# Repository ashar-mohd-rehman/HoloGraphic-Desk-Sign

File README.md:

# HoloGraphic-Desk-Sign
# Assembly 

a holographic desk sign which uses usb c as its power source and displays cool holograms. Custom edge-lit acrylic desk sign displaying death star. Powered via a 5V USB-C interface with low-current 470ohm resistors for safe and cool desk lamp. It sits inside a custom designed 3d printed case with slot to change the sign and a push button to switch it on/off

# PCB 

# Schematic

# case

# Laser Sign 

Bom Link : https://docs.google.com/spreadsheets/d/16aCT9J3KGzLhZE3Ovagxlka1-57kigsySBzX7_v0wDE/edit?usp=sharing

# Bill of Materials (BOM)

| Item | Quantity | Price (USD) | Link |
|------|----------|-------------|------|
| USB Type-C 16-Pin | 1 | $0.41 | [Buy](https://robu.in/product/type-c-31-m-12-hroparts-5a-1-16p-female-type-c-smd-usb-connectors-rohs/) |
| 12mm Tactile Push Button | 10 | $0.47 | [Buy](https://robu.in/product/12x12x12mm-tactile-push-button-switch-10pcs/) |
| LED Kit | 500 | $3.70 | [Buy](https://robu.in/product/pro-range-500pcs-5-colors-f5-mm-led-kit/) |
| 470Ω Resistor | 10 | $0.11 | [Buy](https://robu.in/product/470-ohm-0-25w-metal-film-resistor-pack-of-100/) |
| 5.1kΩ Resistor | 10 | $0.24 | [Buy](https://robu.in/product/mccfr0s2j0512a20-multicomp-pro-carbon-film-resistor-5-1kohm-500mw-5/) |
| PCB | 5 | $2.00 | [JLCPCB Quote](https://cart.jlcpcb.com/quote) |
| SLA Resin 3D Printed Sign | 1 | $2.91 | [JLC3DP Quote](https://jlc3dp.com/3d-printing-quote) |
| Printing Legion Case Estimate | 1 | $1.00 | Printing Estimate |

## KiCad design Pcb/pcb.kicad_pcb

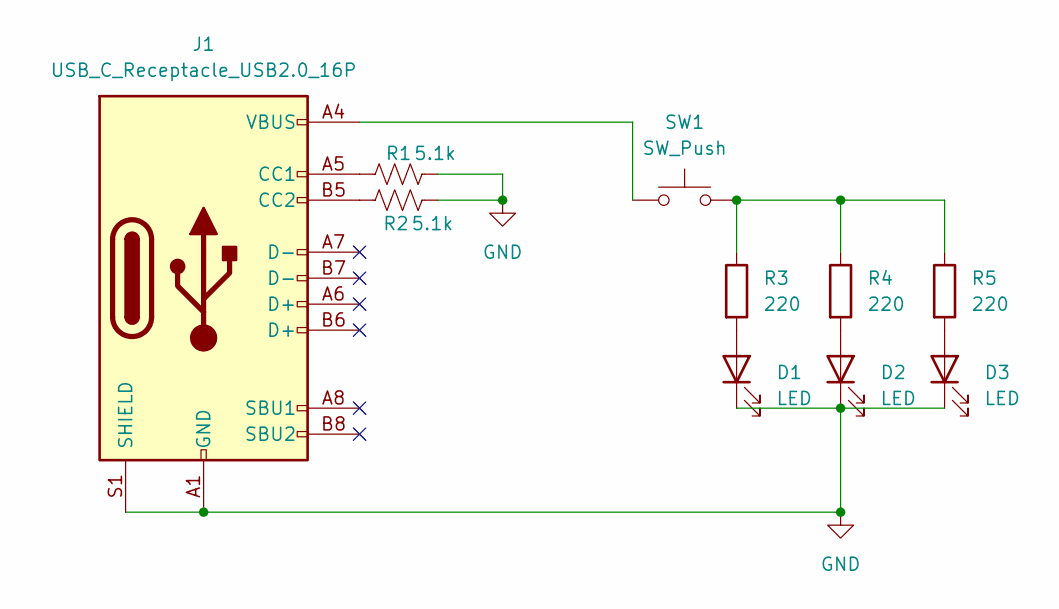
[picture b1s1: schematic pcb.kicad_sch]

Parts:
D1, D2, D3: LED; LED_D5.0mm
J1: USB_C_Receptacle_USB2.0_16P; USB_C_Receptacle_GCT_USB4105-xx-A_16P_TopMnt_Horizontal
R1, R2: 5.1k; R_Axial_DIN0207_L6.3mm_D2.5mm_P7.62mm_Horizontal
R3, R4, R5: 220; R_Axial_DIN0207_L6.3mm_D2.5mm_P7.62mm_Horizontal
SW1: SW_Push; SW_PUSH-12mm

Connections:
GND: D1.1 (K), D2.1 (K), D3.1 (K), J1.A1 (GND), J1.A12 (GND), J1.B1 (GND), J1.B12 (GND), J1.S1 (SHIELD), R1.2, R2.2
unnamed: D1.2 (A), R3.2
unnamed: D2.2 (A), R4.2
unnamed: D3.2 (A), R5.2
unnamed: J1.A5 (CC1), R1.1
unnamed: J1.B5 (CC2), R2.1
unnamed: J1.A4 (VBUS), J1.A9 (VBUS), J1.B4 (VBUS), J1.B9 (VBUS), SW1.1
unnamed: R3.1, R4.1, R5.1, SW1.2

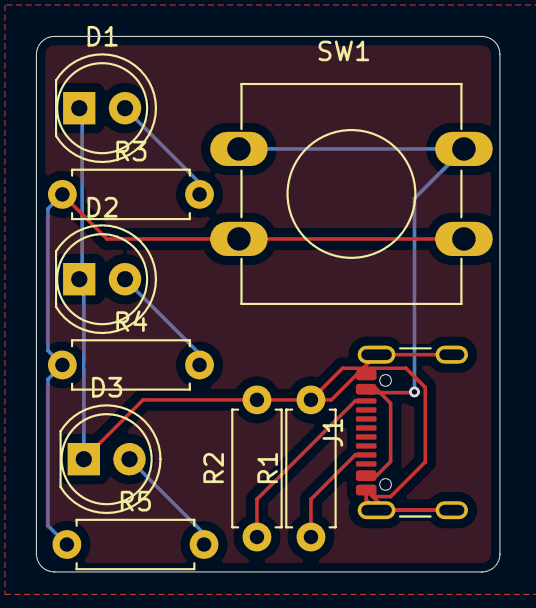
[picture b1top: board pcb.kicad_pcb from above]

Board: 2 copper layers, 25.8 x 29.8 mm, 10 parts (0 on the bottom side), 8 nets.

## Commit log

2026-06-13 Rename pcb.kicad_pcb to Pcb/pcb.kicad_pcb
2026-06-13 Rename pcb.kicad_pro to pcb/pcb.kicad_pro
2026-06-13 Rename pcb.kicad_sch to Pcb/pcb.kicad_sch
2026-06-13 Rename Business_Card.zip to gerber.zip
2026-06-13 Rename Untitled spreadsheet - Sheet1.csv to desk sign.csv
2026-06-13 Rename Case Desk Sign.step to CAD/Case Desk Sign.step
2026-06-13 Rename desk sign.csv to BOM.csv
